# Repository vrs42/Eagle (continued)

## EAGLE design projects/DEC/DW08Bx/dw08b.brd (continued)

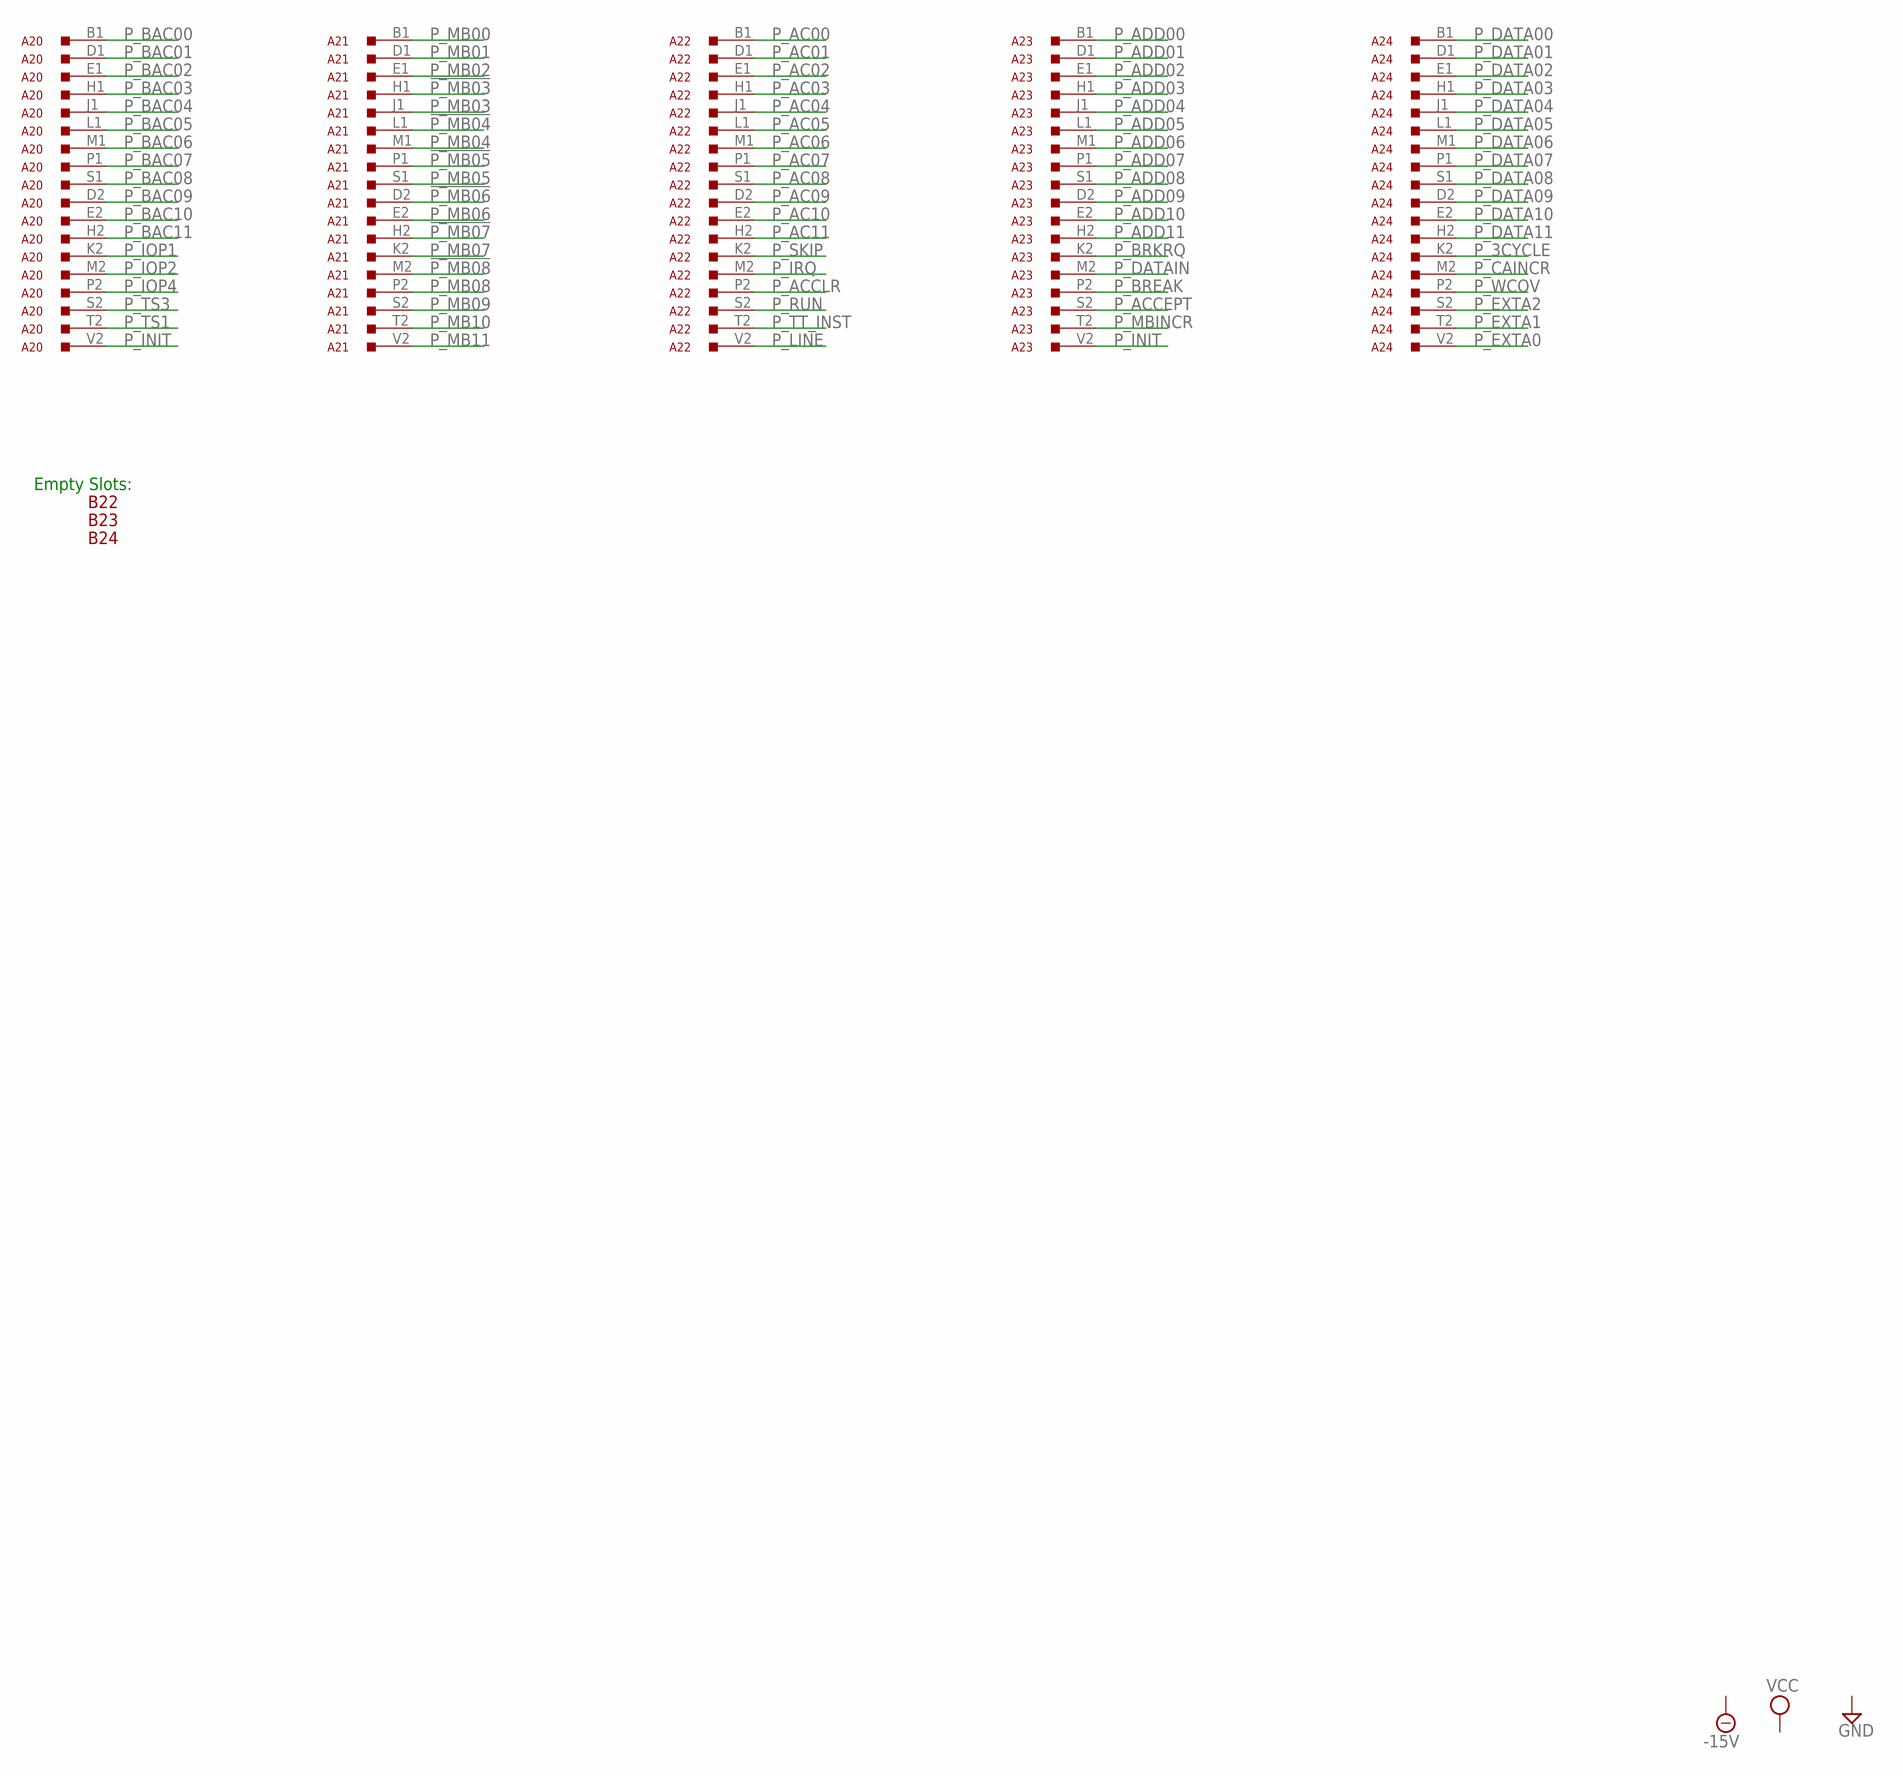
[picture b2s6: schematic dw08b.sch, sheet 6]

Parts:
A20, A21, A22, A23, A24: M903; H807
B22, B23, B24: H807

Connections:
!P_MB03: A21.H1; also elsewhere on the board
!P_MB04: A21.L1; also elsewhere on the board
!P_MB05: A21.P1; also elsewhere on the board
!P_MB06: A21.D2; also elsewhere on the board
!P_MB07: A21.H2; also elsewhere on the board
!P_MB08: A21.M2; also elsewhere on the board
GND: A20.A1 (GND), A20.C1 (GND), A20.C2 (GND), A20.F1 (GND), A20.F2 (GND), A20.J2 (GND), A20.K1 (GND), A20.L2 (GND), A20.N1 (GND), A20.N2 (GND), A20.R1 (GND), A20.R2 (GND), A20.T1 (GND), A20.U2 (GND), A21.A1 (GND), A21.C1 (GND), A21.C2 (GND), A21.F1 (GND), A21.F2 (GND), A21.J2 (GND), A21.K1 (GND), A21.L2 (GND), A21.N1 (GND), A21.N2 (GND), A21.R1 (GND), A21.R2 (GND), A21.T1 (GND), A21.U2 (GND), A22.A1 (GND), A22.C1 (GND), A22.C2 (GND), A22.F1 (GND), A22.F2 (GND), A22.J2 (GND), A22.K1 (GND), A22.L2 (GND), A22.N1 (GND), A22.N2 (GND), A22.R1 (GND), A22.R2 (GND), A22.T1 (GND), A22.U2 (GND), A23.A1 (GND), A23.C1 (GND), A23.C2 (GND), A23.F1 (GND), A23.F2 (GND), A23.J2 (GND), A23.K1 (GND), A23.L2 (GND), A23.N1 (GND), A23.N2 (GND), A23.R1 (GND), A23.R2 (GND), A23.T1 (GND), A23.U2 (GND), A24.A1 (GND), A24.C1 (GND), A24.C2 (GND), A24.F1 (GND), A24.F2 (GND), A24.J2 (GND), A24.K1 (GND), A24.L2 (GND), A24.N1 (GND), A24.N2 (GND), A24.R1 (GND), A24.R2 (GND), A24.T1 (GND), A24.U2 (GND); also elsewhere on the board
P_3CYCLE: A24.K2; also elsewhere on the board
P_AC00: A22.B1; also elsewhere on the board
P_AC01: A22.D1; also elsewhere on the board
P_AC02: A22.E1; also elsewhere on the board
P_AC03: A22.H1; also elsewhere on the board
P_AC04: A22.J1; also elsewhere on the board
P_AC05: A22.L1; also elsewhere on the board
P_AC06: A22.M1; also elsewhere on the board
P_AC07: A22.P1; also elsewhere on the board
P_AC08: A22.S1; also elsewhere on the board
P_AC09: A22.D2; also elsewhere on the board
P_AC10: A22.E2; also elsewhere on the board
P_AC11: A22.H2; also elsewhere on the board
P_ACCEPT: A23.S2; also elsewhere on the board
P_ACCLR: A22.P2; also elsewhere on the board
P_ADD00: A23.B1; also elsewhere on the board
P_ADD01: A23.D1; also elsewhere on the board
P_ADD02: A23.E1; also elsewhere on the board
P_ADD03: A23.H1; also elsewhere on the board
P_ADD04: A23.J1; also elsewhere on the board
P_ADD05: A23.L1; also elsewhere on the board
P_ADD06: A23.M1; also elsewhere on the board
P_ADD07: A23.P1; also elsewhere on the board
P_ADD08: A23.S1; also elsewhere on the board
P_ADD09: A23.D2; also elsewhere on the board
P_ADD10: A23.E2; also elsewhere on the board
P_ADD11: A23.H2; also elsewhere on the board
P_BAC00: A20.B1; also elsewhere on the board
P_BAC01: A20.D1; also elsewhere on the board
P_BAC02: A20.E1; also elsewhere on the board
P_BAC03: A20.H1; also elsewhere on the board
P_BAC04: A20.J1; also elsewhere on the board
P_BAC05: A20.L1; also elsewhere on the board
P_BAC06: A20.M1; also elsewhere on the board
P_BAC07: A20.P1; also elsewhere on the board
P_BAC08: A20.S1; also elsewhere on the board
P_BAC09: A20.D2; also elsewhere on the board
P_BAC10: A20.E2; also elsewhere on the board
P_BAC11: A20.H2; also elsewhere on the board
P_BREAK: A23.P2; also elsewhere on the board
P_BRKRQ: A23.K2; also elsewhere on the board
P_CAINCR: A24.M2; also elsewhere on the board
P_DATA00: A24.B1; also elsewhere on the board
P_DATA01: A24.D1; also elsewhere on the board
P_DATA02: A24.E1; also elsewhere on the board
P_DATA03: A24.H1; also elsewhere on the board
P_DATA04: A24.J1; also elsewhere on the board
P_DATA05: A24.L1; also elsewhere on the board
P_DATA06: A24.M1; also elsewhere on the board
P_DATA07: A24.P1; also elsewhere on the board
P_DATA08: A24.S1; also elsewhere on the board
P_DATA09: A24.D2; also elsewhere on the board
P_DATA10: A24.E2; also elsewhere on the board
P_DATA11: A24.H2; also elsewhere on the board
P_DATAIN: A23.M2; also elsewhere on the board
P_EXTA0: A24.V2; also elsewhere on the board
P_EXTA1: A24.T2; also elsewhere on the board
P_EXTA2: A24.S2; also elsewhere on the board
P_INIT: A20.V2, A23.V2; also elsewhere on the board
P_IOP1: A20.K2; also elsewhere on the board
P_IOP2: A20.M2; also elsewhere on the board
P_IOP4: A20.P2; also elsewhere on the board
P_IRQ: A22.M2; also elsewhere on the board
P_LINE: A22.V2; also elsewhere on the board
P_MB00: A21.B1; also elsewhere on the board
P_MB01: A21.D1; also elsewhere on the board
P_MB02: A21.E1; also elsewhere on the board
P_MB03: A21.J1; also elsewhere on the board
P_MB04: A21.M1; also elsewhere on the board
P_MB05: A21.S1; also elsewhere on the board
P_MB06: A21.E2; also elsewhere on the board
P_MB07: A21.K2; also elsewhere on the board
P_MB08: A21.P2; also elsewhere on the board
P_MB09: A21.S2; also elsewhere on the board
P_MB10: A21.T2; also elsewhere on the board
P_MB11: A21.V2; also elsewhere on the board
P_MBINCR: A23.T2; also elsewhere on the board
P_RUN: A22.S2; also elsewhere on the board
P_SKIP: A22.K2; also elsewhere on the board
P_TS1: A20.T2; also elsewhere on the board
P_TS3: A20.S2; also elsewhere on the board
P_TT_INST: A22.T2; also elsewhere on the board
P_WCOV: A24.P2; also elsewhere on the board

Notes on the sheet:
Empty Slots:

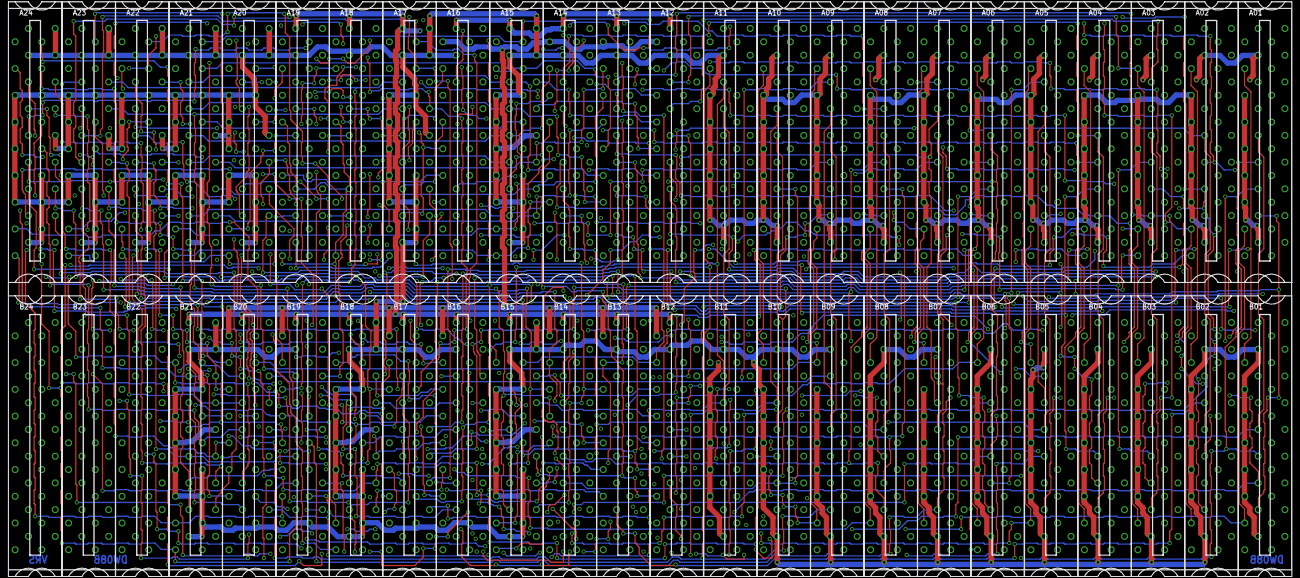
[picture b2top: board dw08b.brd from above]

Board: 4 copper layers, 304.8 x 133.3 mm, 48 parts (0 on the bottom side), 188 nets.
